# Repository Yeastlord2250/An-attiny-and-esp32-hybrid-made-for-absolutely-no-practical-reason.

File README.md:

# An-attiny-and-esp32-hybrid-made-for-absolutely-no-practical-reason.
An attiny and esp32 hybrid made for absolutely no practical reason.

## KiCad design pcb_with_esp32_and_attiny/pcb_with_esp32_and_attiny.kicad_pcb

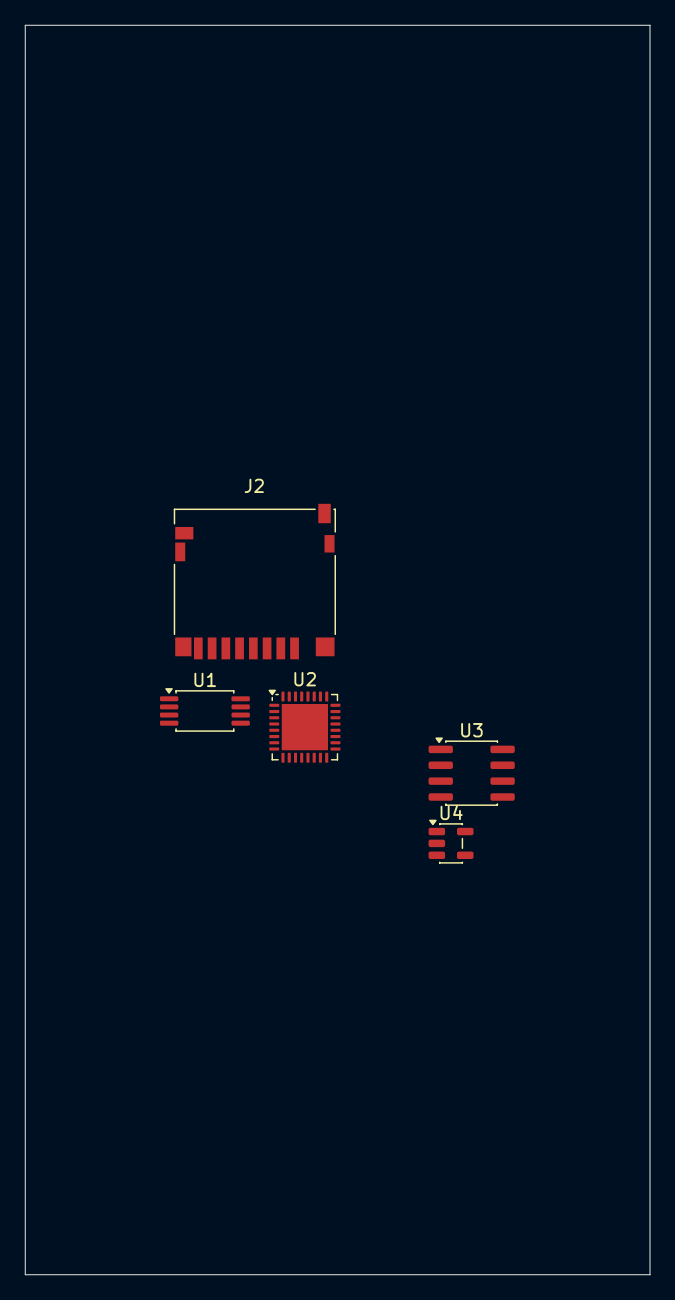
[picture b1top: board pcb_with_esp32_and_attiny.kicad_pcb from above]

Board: 2 copper layers, 50.0 x 100.0 mm, 5 parts (0 on the bottom side), 2 nets, no tracks yet.

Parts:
J2: Micro_SD_Card; microSD_HC_Hirose_DM3D-SF
U1: ATtiny45-20X; TSSOP-8_4.4x3mm_P0.65mm
U2: ESP32-C3; QFN-32-1EP_5x5mm_P0.5mm_EP3.7x3.7mm
U3: IS66WVS4M8BLL-104NLI-TR; SOIC-8_3.9x4.9mm_P1.27mm
U4: AP2127K-3.3; SOT-23-5

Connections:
unnamed: U2.2 (VDD3P3), U2.3 (VDD3P3)
unnamed: U2.31 (VDDA), U2.32 (VDDA)
